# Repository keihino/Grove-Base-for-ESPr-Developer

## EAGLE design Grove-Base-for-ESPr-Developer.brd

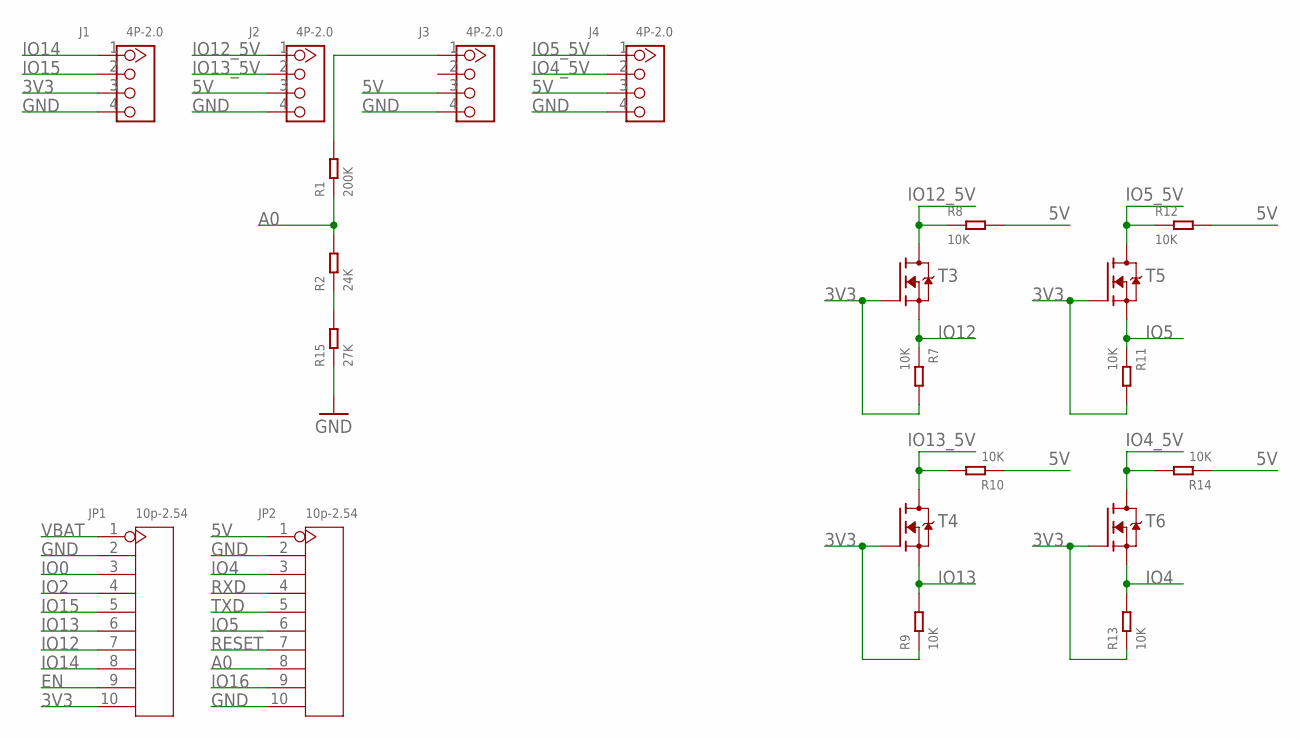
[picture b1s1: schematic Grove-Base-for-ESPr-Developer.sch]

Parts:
J1, J2, J3, J4: 4P-2.0; HW4-2.0
JP1, JP2: 10p-2.54; H10-2.54
R1: 200K; R0603
R2: 24K; R0603
R7, R8, R9, R10, R11, R12, R13, R14: 10K; R0603
R15: 27K; R0603
T3, T4, T5, T6: MOSFET-N-SOT23; SOT23

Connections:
3V3: J1.3, JP1.10, R7.2, R9.1, R11.2, R13.1, T3.1 (G), T4.1 (G), T5.1 (G), T6.1 (G)
5V: J2.3, J3.3, J4.3, JP2.1, R8.2, R10.1, R12.2, R14.1
A0: JP2.8, R1.1, R2.2
EN: JP1.9
GND: J1.4, J2.4, J3.4, J4.4, JP1.2, JP2.2, JP2.10, R15.1
IO0: JP1.3
IO2: JP1.4
IO4: JP2.3, R13.2, T6.2 (S)
IO4_5V: J4.2, R14.2, T6.3 (D)
IO5: JP2.6, R11.1, T5.2 (S)
IO5_5V: J4.1, R12.1, T5.3 (D)
IO12: JP1.7, R7.1, T3.2 (S)
IO12_5V: J2.1, R8.1, T3.3 (D)
IO13: JP1.6, R9.2, T4.2 (S)
IO13_5V: J2.2, R10.2, T4.3 (D)
IO14: J1.1, JP1.8
IO15: J1.2, JP1.5
IO16: JP2.9
unnamed: J3.1, R1.2
unnamed: R2.1, R15.2
RESET: JP2.7
RXD: JP2.4
TXD: JP2.5
VBAT: JP1.1

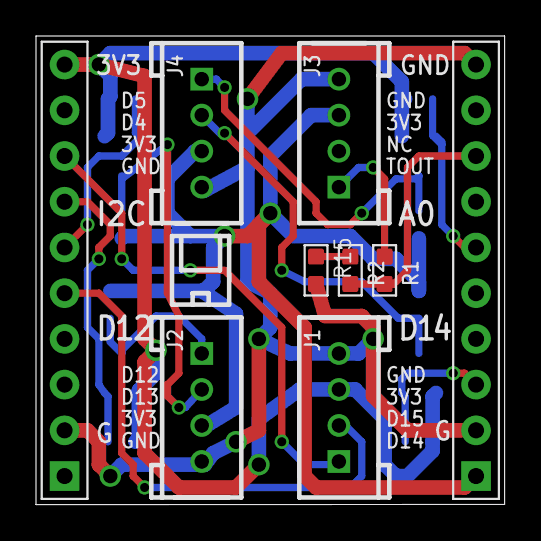
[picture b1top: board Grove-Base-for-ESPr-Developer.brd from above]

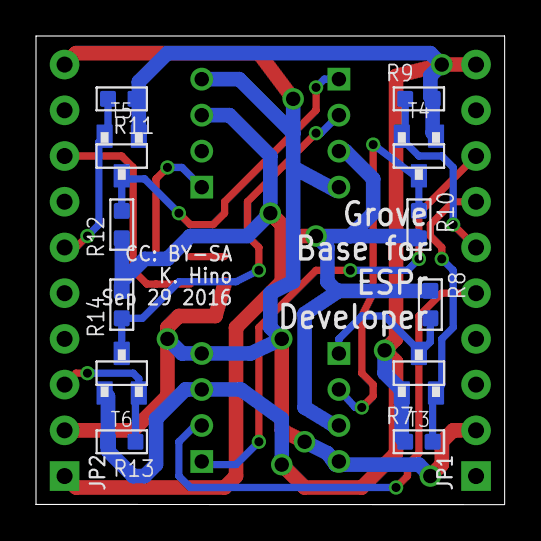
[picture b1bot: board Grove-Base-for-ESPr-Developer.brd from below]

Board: 2 copper layers, 26.0 x 26.0 mm, 21 parts (12 on the bottom side), 16 nets.

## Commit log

2016-10-04 1st 5V evt
2016-10-11 2nd EVT
    2nd EVT (for hand soldering...)
